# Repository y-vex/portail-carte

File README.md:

# Carte de commande pour portail à deux moteurs 24 V, avec HomeKit

Carte électronique et firmware pour piloter un portail motorisé à **deux vantaux et deux moteurs 24 V à courant
continu**, sans capteur de fin de course. Elle remplace une carte de commande du commerce tombée en panne et ajoute
Apple HomeKit, une page web de réglage et un journal des événements.

Elle a été conçue pour un portail coulissant autoportant Portaleco CT08APO-02, à deux vantaux et ouverture centrale, équipé de deux moteurs Nidec 404.854
(24 V DC), où elle remplace une carte Prastel UNIK2E.

> **Avertissement.** Un portail motorisé peut blesser gravement. Ce projet est un travail personnel, publié tel quel,
> sans aucune garantie. Il n'a fait l'objet d'aucune certification et **ne remplace pas les sécurités exigées pour un
> portail motorisé** (photocellules, limitation d'effort vérifiée à l'instrument, conformité aux normes en vigueur,
> dont l'EN 12453 en Europe). Si vous le reproduisez, vous le faites sous votre seule responsabilité.

## État du projet

- Carte **v0.4** fabriquée et assemblée, en service sur un portail coulissant Portaleco depuis novembre 2026.
- Essayé sur ce portail : mouvements complets, apprentissage des courses, détection d'obstacle par le courant
  (fermeture), photocellule (réouverture quand le faisceau est coupé à la fermeture), feu clignotant, arrêt
  progressif, HomeKit, page web, journal, mise à jour par le Wi-Fi.
- Pas encore essayé sur ce portail : entrée STOP, entrée radio,
  détection d'obstacle à l'ouverture avec un obstacle réel.
- Limite connue : par temps froid (quelques degrés), le courant des moteurs monte et s'approche des seuils appris
  par temps doux ; une fausse détection d'obstacle s'est produite une fois à l'ouverture. Les seuils sont à revoir
  selon la saison.
- Un seul portail, un seul modèle de moteur : les réglages par défaut sont des points de départ.

## La carte

| | |
| --- | --- |
| Alimentation | 24 V DC régulé (bornier J1), fusible général 15 A, protection contre l'inversion, écrêteur de surtension |
| Moteurs | 2 × pont en H TI DRV8245S réglé par SPI (borniers J2, J3), fusible 10 A par moteur, mesure du courant |
| Microcontrôleur | ESP32-S3-WROOM-1-N8, USB-C |
| Entrées (J4) | pas à pas, photocellule, radio, STOP : contacts secs, isolés par optocoupleurs, alimentés en 12 V |
| Sorties (J5) | feu clignotant et sortie auxiliaire, 12 V, commutées côté masse |
| Dimensions | 150 × 100 mm, deux couches |

- Schéma : [`schema.pdf`](schema.pdf). `schema-lisible.html` en donne une version simplifiée, par fonction
  (alimentation, commande d'un moteur, une entrée, une sortie), pour qui ne lit pas un schéma électronique.
- Projet KiCad : `kicad/`. Fichiers de fabrication : `fabrication/` et `portail-gerber.zip`.
- Nomenclature : `nomenclature.csv` ; variantes pour l'assemblage dans `fabrication/`.

**Câblage des entrées : attention au sens.** Chaque contact se branche entre `+12V_ACC` et son entrée (`PP`, `FOTO`,
`RADIO`, `STOP`). Beaucoup de cartes du commerce font l'inverse, avec des contacts qui se ferment vers un commun relié
à la masse. Un accessoire câblé pour une telle carte, par exemple un récepteur de photocellule dont le commun du
contact est ponté sur le moins de son alimentation, doit être recâblé : commun du contact sur le +12 V.
Les charges des sorties se branchent entre `+12V_OUT` et `LAMP_N` ou `AUX_N` (environ 1 A au total).

Le schéma et le circuit imprimé ne sont pas dessinés à la main : ils sont **générés par les scripts Python** de `gen/`
(`build.py` décrit le circuit, `pcb_all.py` place, route avec Freerouting et lance le contrôle des règles).

## Le firmware

Dans `firmware/portail/`, pour Arduino-ESP32 avec la bibliothèque [HomeSpan](https://github.com/HomeSpan/HomeSpan).
La notice complète est dans [`firmware/portail/LISEZMOI.md`](firmware/portail/LISEZMOI.md).

- Position estimée par le temps de fonctionnement, recalée à chaque butée.
- Butée et obstacle détectés par le courant des moteurs ; à la fermeture, un obstacle provoque la réouverture.
- Apprentissage automatique des courses et des seuils de blocage.
- Démarrage, ralentissement avant les butées et arrêt commandé progressifs.
- HomeKit : accessoire « porte de garage », plus deux capteurs d'alerte (défaut, portail resté ouvert).
- Page web sur le port 8080 : état, mesures, commandes, réglages, journal, sauvegarde et restauration des réglages.

```bash
cd firmware/portail
arduino-cli compile -b esp32:esp32:esp32s3:CDCOnBoot=cdc,FlashSize=8M,PartitionScheme=default_8MB .
arduino-cli upload  -b esp32:esp32:esp32s3:CDCOnBoot=cdc,FlashSize=8M,PartitionScheme=default_8MB -p <port> .
```

Versions utilisées : cœur `esp32:esp32` 3.3.12, HomeSpan 2.1.8.

### Sécurité réseau : à lire avant la mise en service

- La page web **n'a pas de mot de passe** : tout appareil du réseau local peut commander le portail. Ne l'exposez
  jamais sur Internet.
- La mise à jour par le Wi-Fi utilise le mot de passe par défaut de HomeSpan tant que vous ne l'avez pas changé
  (commande `O` de la console série). Changez-le, ainsi que le code d'appairage HomeKit (commande `S`).

## Régénérer la carte

Prérequis utilisés : KiCad 7 (`kicad-cli` et module Python `pcbnew`), Java 21, `xvfb-run`, Python 3 avec `cairosvg`
et `Pillow`, sous Linux. Les chemins des bibliothèques KiCad sont en dur dans `gen/kisch.py` et `gen/pcb_build.py`.
Freerouting 1.9.0 n'est pas inclus : téléchargez `freerouting.jar` depuis
[le dépôt de Freerouting](https://github.com/freerouting/freerouting) et placez-le dans `tools/`.

```bash
python3 gen/build.py        # schéma et nomenclature
python3 gen/check.py        # doit afficher OK
python3 gen/pcb_all.py      # placement, routage, contrôle des règles (plusieurs minutes)
```

## Licences

- **Matériel** (schéma, circuit imprimé, fichiers de fabrication, nomenclature, images) :
  [CERN-OHL-S v2](LICENSES/CERN-OHL-S-2.0.txt), partage à l'identique.
- **Logiciel** (firmware et scripts de `gen/`) : [GPL version 3 ou ultérieure](LICENSES/GPL-3.0-or-later.txt).

Détail et éléments tiers dans [`LICENSE.md`](LICENSE.md).

Ce projet est indépendant : il n'est ni affilié à Portaleco, Prastel, Nidec ou Apple, ni approuvé par eux. Les marques
citées appartiennent à leurs propriétaires et ne sont mentionnées que pour décrire le matériel utilisé.

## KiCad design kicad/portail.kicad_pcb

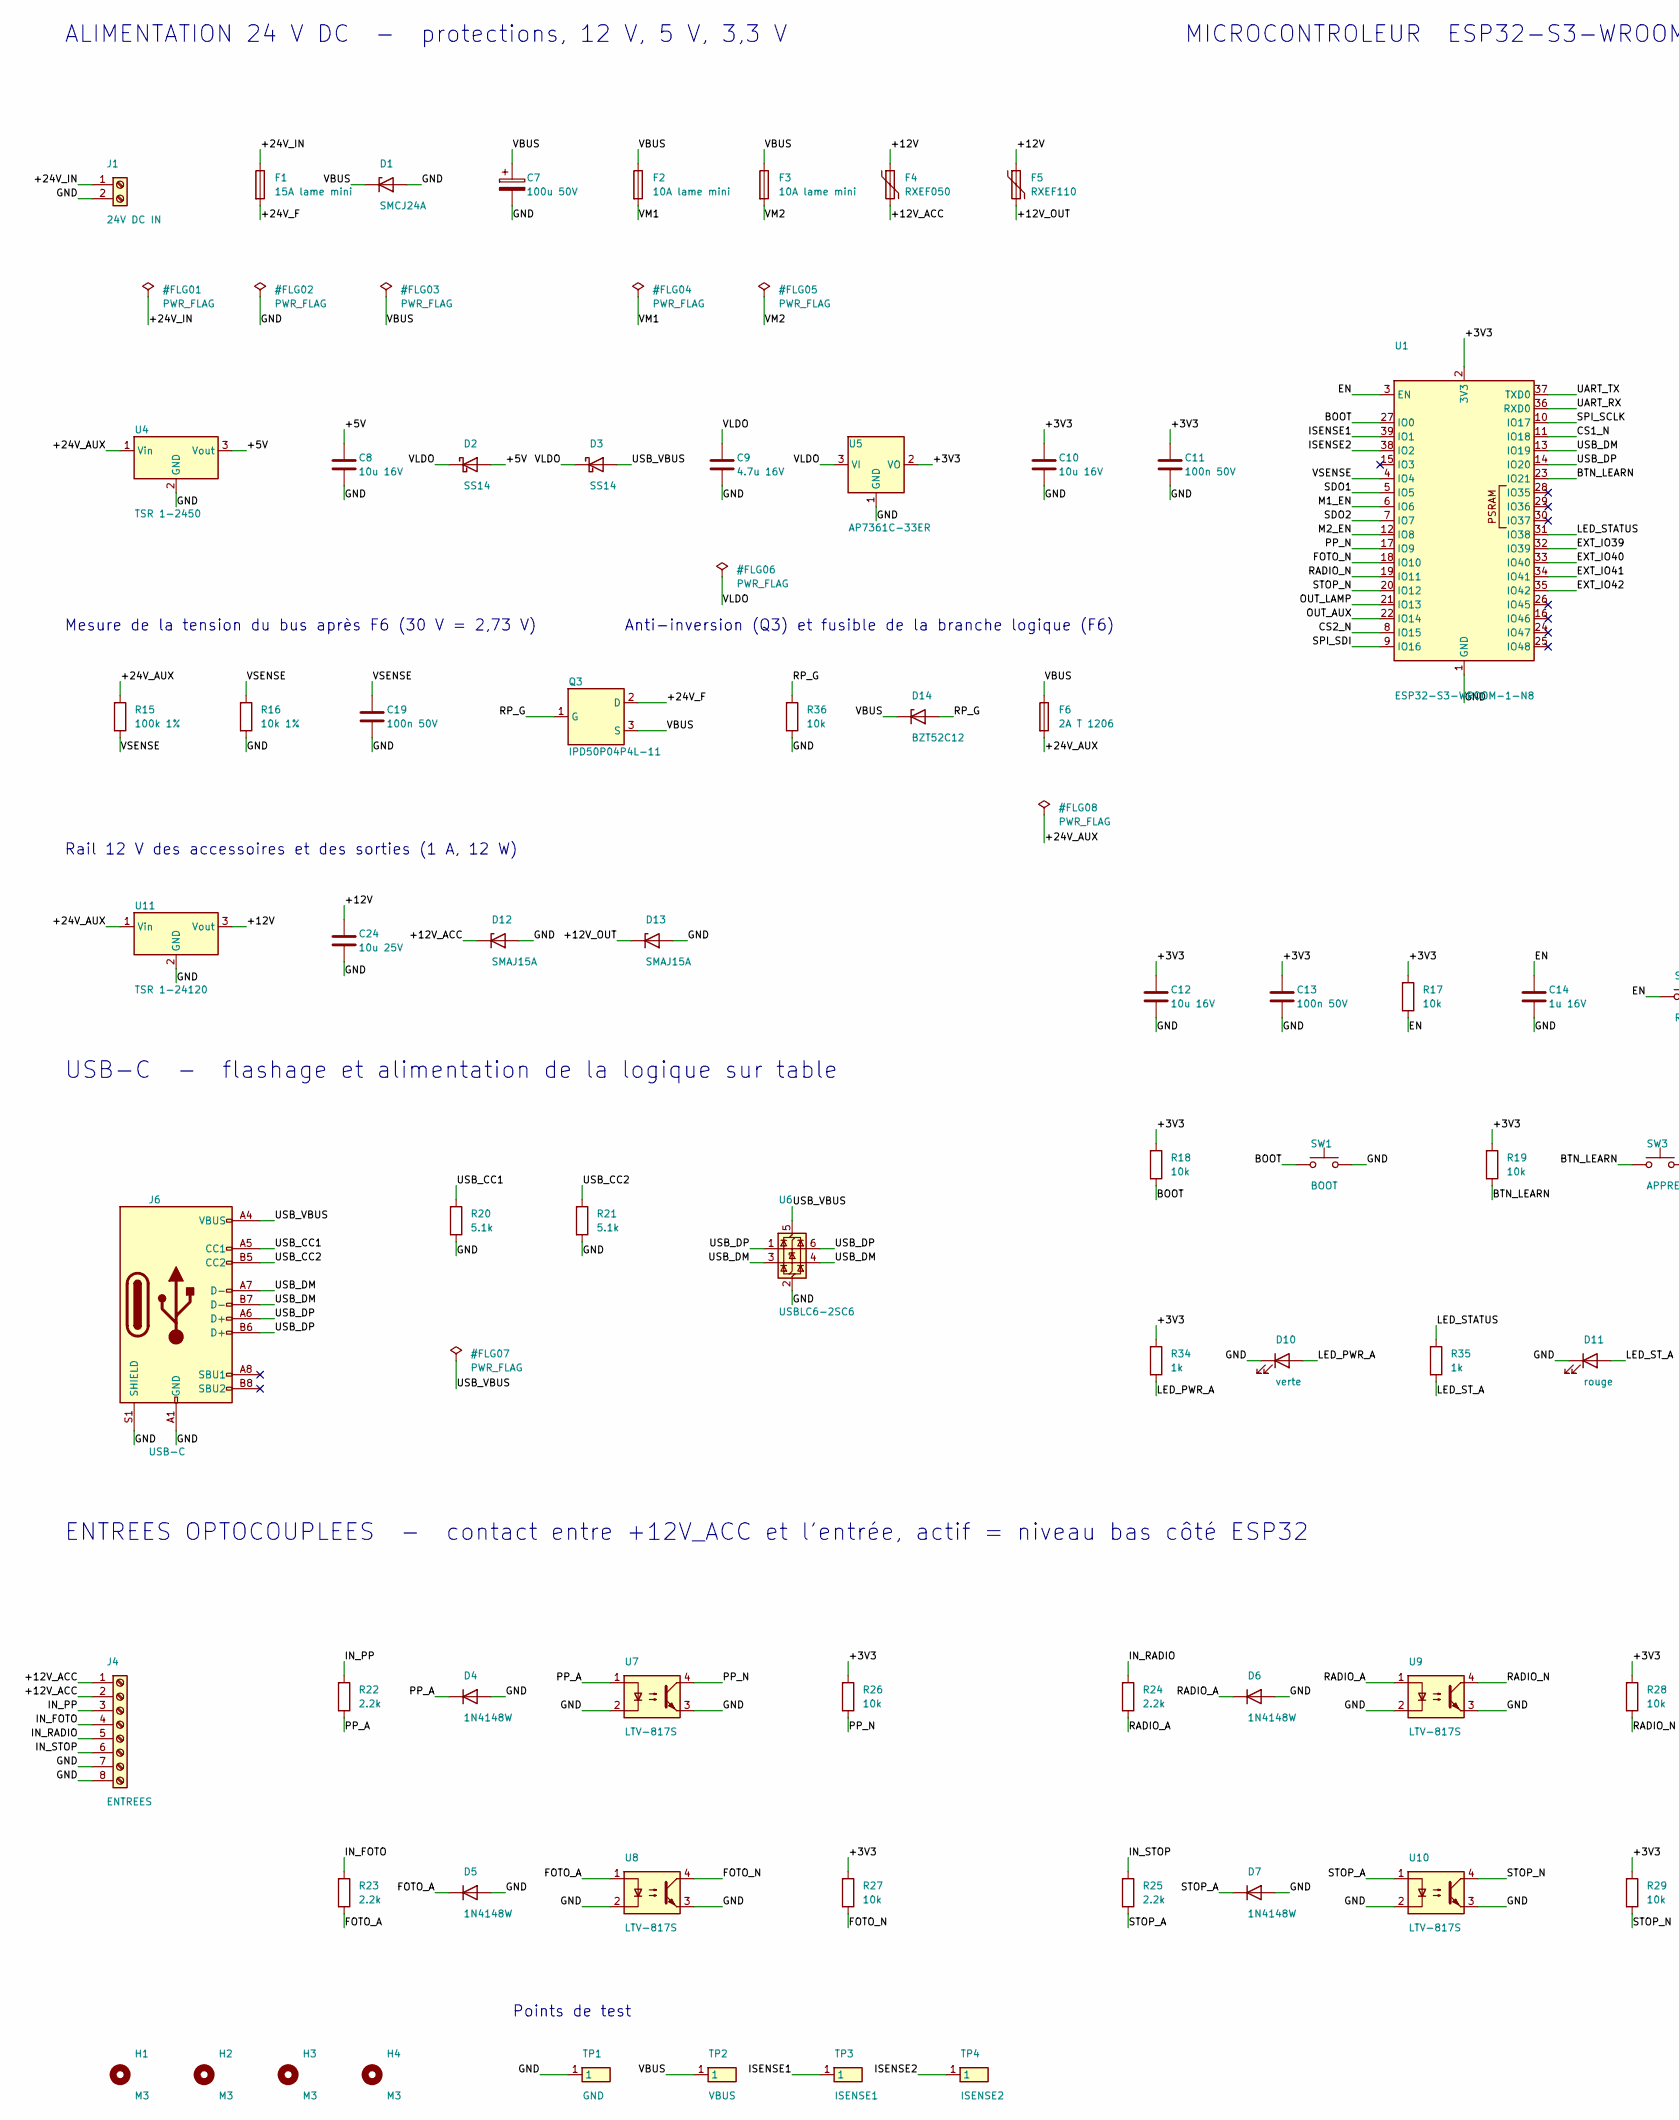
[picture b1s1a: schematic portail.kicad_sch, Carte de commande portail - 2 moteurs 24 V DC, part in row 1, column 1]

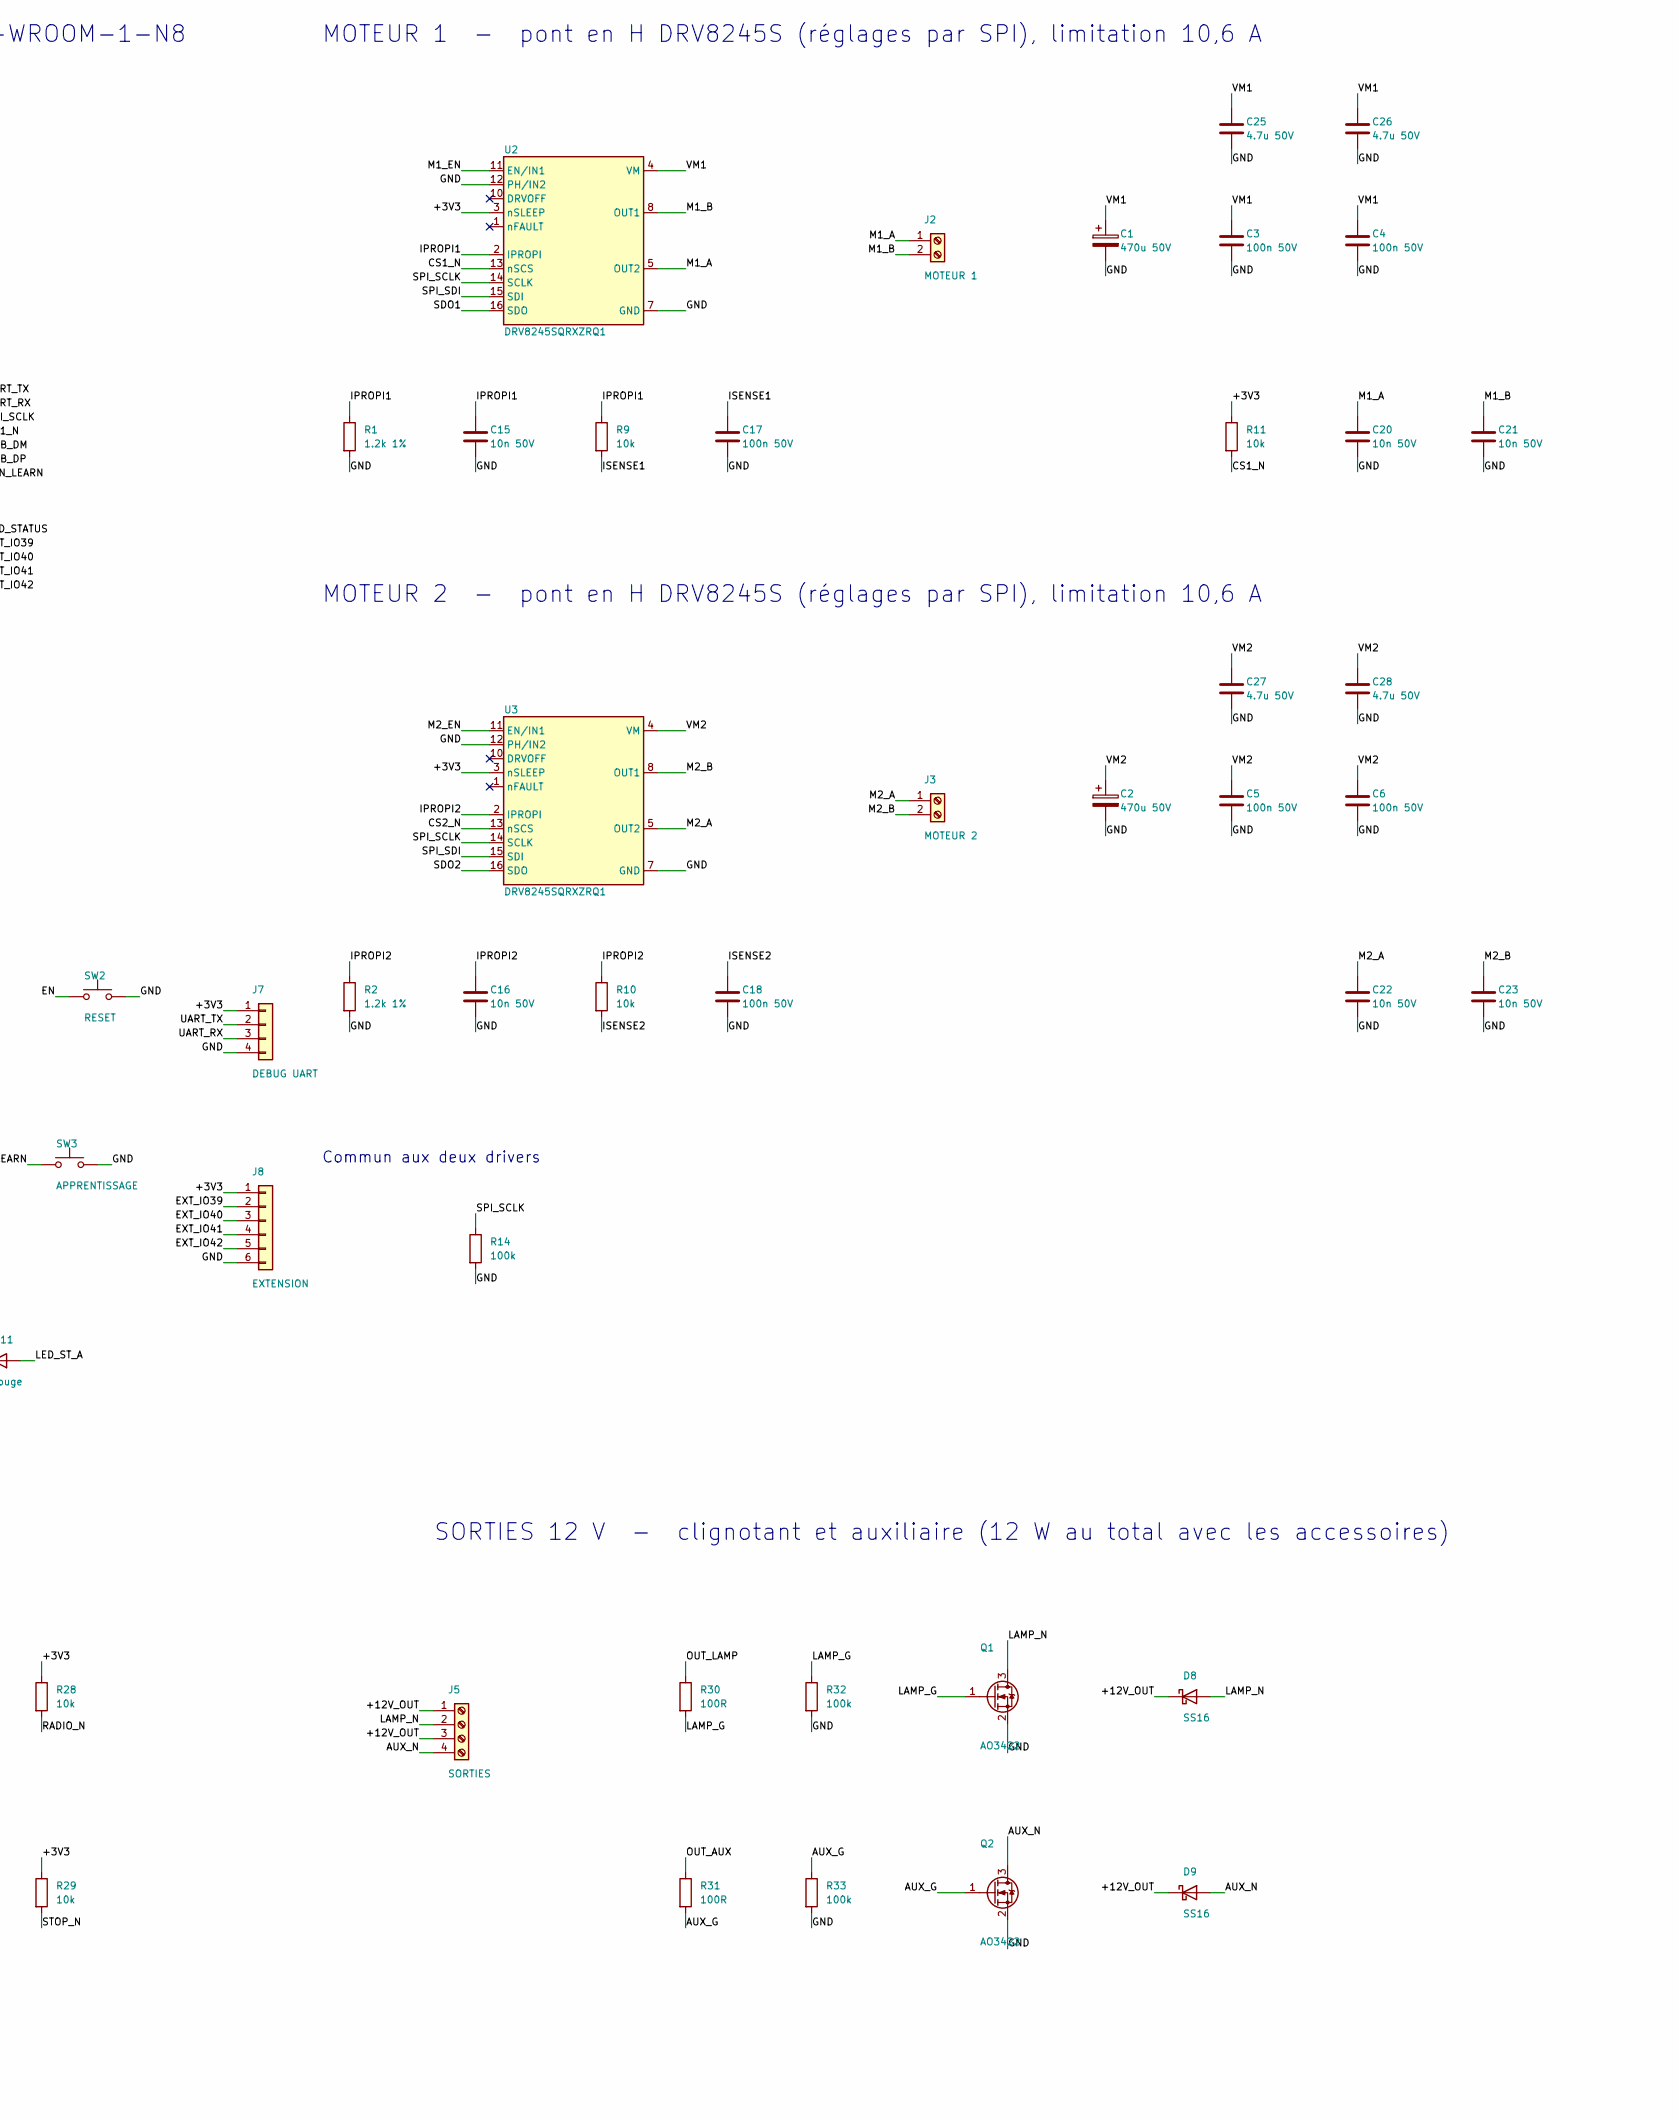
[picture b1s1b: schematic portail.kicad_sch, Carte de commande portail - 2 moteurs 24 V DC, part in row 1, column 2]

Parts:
C1, C2: 470u 50V; CP_Radial_D10.0mm_P5.00mm
C3, C4, C5, C6, C11, C13, C17, C18, C19: 100n 50V; C_0603_1608Metric
C7: 100u 50V; CP_Radial_D8.0mm_P3.50mm
C8, C10, C12: 10u 16V; C_0805_2012Metric
C9: 4.7u 16V; C_0805_2012Metric
C14: 1u 16V; C_0603_1608Metric
C15, C16, C20, C21, C22, C23: 10n 50V; C_0603_1608Metric
C24: 10u 25V; C_1206_3216Metric
C25, C26, C27, C28: 4.7u 50V; C_1206_3216Metric; MPN GRM31CR71H475KA12
D1: SMCJ24A; D_SMC; MPN SMCJ24A
D2, D3: SS14; D_SMA; MPN SS14
D4, D5, D6, D7: 1N4148W; D_SOD-123; MPN 1N4148W
D8, D9: SS16; D_SMA; MPN SS16
D10: verte; LED_0603_1608Metric
D11: rouge; LED_0603_1608Metric
D12, D13: SMAJ15A; D_SMA; MPN SMAJ15A
D14: BZT52C12; D_SOD-123; MPN BZT52C12
F1: 15A lame mini; Fuseholder_Blade_Mini_Keystone_3568
F2, F3: 10A lame mini; Fuseholder_Blade_Mini_Keystone_3568
F4: RXEF050; C_Disc_D10.5mm_W5.0mm_P5.00mm; MPN RXEF050
F5: RXEF110; C_Disc_D10.5mm_W5.0mm_P5.00mm; MPN RXEF110
F6: 2A T 1206; Fuse_1206_3216Metric; MPN 0468002.NR
H1, H2, H3, H4: M3; MountingHole_3.2mm_M3
J1: 24V DC IN; TerminalBlock_Phoenix_MKDS-1,5-2-5.08_1x02_P5.08mm_Horizont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
J2: MOTEUR 1; TerminalBlock_Phoenix_MKDS-1,5-2-5.08_1x02_P5.08mm_Horizont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
J3: MOTEUR 2; TerminalBlock_Phoenix_MKDS-1,5-2-5.08_1x02_P5.08mm_Horizont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
J4: ENTREES; TerminalBlock_Phoenix_PT-1,5-8-3.5-H_1x08_P3.50mm_Horizontal
J5: SORTIES; TerminalBlock_Phoenix_PT-1,5-4-3.5-H_1x04_P3.50mm_Horizontal
J6: USB-C; USB_C_Receptacle_GCT_USB4105-xx-A_16P_TopMnt_Horizontal; MPN USB4105-GF-A
J7: DEBUG UART; PinHeader_1x04_P2.54mm_Vertical
J8: EXTENSION; PinHeader_1x06_P2.54mm_Vertical
Q1, Q2: AO3422; SOT-23; MPN AO3422
Q3: IPD50P04P4L-11; TO-252-2; MPN IPD90P04P4L-04
R1, R2: 1.2k 1%; R_0603_1608Metric
R9, R10, R11, R17, R18, R19, R26, R27, R28, R29, R36: 10k; R_0603_1608Metric
R14, R32, R33: 100k; R_0603_1608Metric
R15: 100k 1%; R_0603_1608Metric
R16: 10k 1%; R_0603_1608Metric
R20, R21: 5.1k; R_0603_1608Metric
R22, R23, R24, R25: 2.2k; R_1206_3216Metric
R30, R31: 100R; R_0603_1608Metric
R34, R35: 1k; R_0603_1608Metric
SW1: BOOT; SW_SPST_TL3342
SW2: RESET; SW_SPST_TL3342
SW3: APPRENTISSAGE; SW_SPST_TL3342
TP1: GND; TestPoint_Pad_D1.5mm
TP2: VBUS; TestPoint_Pad_D1.5mm
TP3: ISENSE1; TestPoint_Pad_D1.5mm
TP4: ISENSE2; TestPoint_Pad_D1.5mm
U1: ESP32-S3-WROOM-1-N8; ESP32-S3-WROOM-1; MPN ESP32-S3-WROOM-1-N8
U2, U3: DRV8245SQRXZRQ1; DRV8245_VQFN-HR-16_RXZ; MPN DRV8245SQRXZRQ1
U4: TSR 1-2450; Converter_DCDC_TRACO_TSR-1_THT; MPN TSR 1-2450
U5: AP7361C-33ER; SOT-223-3_TabPin2; MPN AP7361C-33ER-13
U6: USBLC6-2SC6; SOT-23-6; MPN USBLC6-2SC6
U7, U8, U9, U10: LTV-817S; SMDIP-4_W9.53mm; MPN LTV-817S
U11: TSR 1-24120; Converter_DCDC_TRACO_TSR-1_THT; MPN TSR 1-24120

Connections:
+3V3: C10.1, C11.1, C12.1, C13.1, J7.1, J8.1, R11.1, R17.1, R18.1, R19.1, R26.1, R27.1, R28.1, R29.1, R34.1, U1.2 (3V3), U2.3 (nSLEEP), U3.3 (nSLEEP), U5.2 (VO)
+5V: C8.1, D2.2 (A), U4.3 (Vout)
+12V: C24.1, F4.1, F5.1, U11.3 (Vout)
+12V_ACC: D12.1 (K), F4.2, J4.1, J4.2
+12V_OUT: D8.1 (K), D9.1 (K), D13.1 (K), F5.2, J5.1, J5.3
+24V_AUX: F6.2, R15.1, U4.1 (Vin), U11.1 (Vin)
+24V_F: F1.2, Q3.2 (D)
+24V_IN: F1.1, J1.1
AUX_G: Q2.1 (G), R31.2, R33.1
AUX_N: D9.2 (A), J5.4, Q2.3 (D)
BOOT: R18.2, SW1.1, U1.27 (IO0)
BTN_LEARN: R19.2, SW3.1, U1.23 (IO21)
CS1_N: R11.2, U1.11 (IO18), U2.13 (nSCS)
CS2_N: U1.8 (IO15), U3.13 (nSCS)
EN: C14.1, R17.2, SW2.1, U1.3 (EN)
EXT_IO39: J8.2, U1.32 (IO39)
EXT_IO40: J8.3, U1.33 (IO40)
EXT_IO41: J8.4, U1.34 (IO41)
EXT_IO42: J8.5, U1.35 (IO42)
FOTO_A: D5.1 (K), R23.2, U8.1
FOTO_N: R27.2, U1.18 (IO10), U8.4
GND: C1.2, C2.2, C3.2, C4.2, C5.2, C6.2, C7.2, C8.2, C9.2, C10.2, C11.2, C12.2, C13.2, C14.2, C15.2, C16.2, C17.2, C18.2, C19.2, C20.2, C21.2, C22.2, C23.2, C24.2, C25.2, C26.2, C27.2, C28.2, D1.2 (A), D4.2 (A), D5.2 (A), D6.2 (A), D7.2 (A), D10.1 (K), D11.1 (K), D12.2 (A), D13.2 (A), J1.2, J4.7, J4.8, J6.A1 (GND), J6.A12 (GND), J6.B1 (GND), J6.B12 (GND), J6.S1 (SHIELD), J7.4, J8.6, Q1.2 (S), Q2.2 (S), R1.2, R2.2, R14.2, R16.2, R20.2, R21.2, R32.2, R33.2, R36.2, SW1.2, SW2.2, SW3.2, TP1.1, U1.1 (GND), U1.40 (GND), U1.41 (GND), U2.7 (GND), U2.12 (PH/IN2), U3.7 (GND), U3.12 (PH/IN2), U4.2 (GND), U5.1 (GND), U6.2 (GND), U7.2, U7.3, U8.2, U8.3, U9.2, U9.3, U10.2, U10.3, U11.2 (GND)
IN_FOTO: J4.4, R23.1
IN_PP: J4.3, R22.1
IN_RADIO: J4.5, R24.1
IN_STOP: J4.6, R25.1
IPROPI1: C15.1, R1.1, R9.1, U2.2 (IPROPI)
IPROPI2: C16.1, R2.1, R10.1, U3.2 (IPROPI)
ISENSE1: C17.1, R9.2, TP3.1, U1.39 (IO1)
ISENSE2: C18.1, R10.2, TP4.1, U1.38 (IO2)
LAMP_G: Q1.1 (G), R30.2, R32.1
LAMP_N: D8.2 (A), J5.2, Q1.3 (D)
LED_PWR_A: D10.2 (A), R34.2
LED_STATUS: R35.1, U1.31 (IO38)
LED_ST_A: D11.2 (A), R35.2
M1_A: C20.1, J2.1, U2.5 (OUT2), U2.6 (OUT2)
M1_B: C21.1, J2.2, U2.8 (OUT1), U2.9 (OUT1)
M1_EN: U1.6 (IO6), U2.11 (EN/IN1)
M2_A: C22.1, J3.1, U3.5 (OUT2), U3.6 (OUT2)
M2_B: C23.1, J3.2, U3.8 (OUT1), U3.9 (OUT1)
M2_EN: U1.12 (IO8), U3.11 (EN/IN1)
OUT_AUX: R31.1, U1.22 (IO14)
OUT_LAMP: R30.1, U1.21 (IO13)
PP_A: D4.1 (K), R22.2, U7.1
PP_N: R26.2, U1.17 (IO9), U7.4
RADIO_A: D6.1 (K), R24.2, U9.1
RADIO_N: R28.2, U1.19 (IO11), U9.4
RP_G: D14.2 (A), Q3.1 (G), R36.1
SDO1: U1.5 (IO5), U2.16 (SDO)
SDO2: U1.7 (IO7), U3.16 (SDO)
SPI_SCLK: R14.1, U1.10 (IO17), U2.14 (SCLK), U3.14 (SCLK)
SPI_SDI: U1.9 (IO16), U2.15 (SDI), U3.15 (SDI)
STOP_A: D7.1 (K), R25.2, U10.1
STOP_N: R29.2, U1.20 (IO12), U10.4
UART_RX: J7.3, U1.36 (RXD0)
UART_TX: J7.2, U1.37 (TXD0)
USB_CC1: J6.A5 (CC1), R20.1
USB_CC2: J6.B5 (CC2), R21.1
USB_DM: J6.A7 (D-), J6.B7 (D-), U1.13 (IO19), U6.3 (I/O2), U6.4 (I/O2)
USB_DP: J6.A6 (D+), J6.B6 (D+), U1.14 (IO20), U6.1 (I/O1), U6.6 (I/O1)
USB_VBUS: D3.2 (A), J6.A4 (VBUS), J6.A9 (VBUS), J6.B4 (VBUS), J6.B9 (VBUS), U6.5 (VBUS)
VBUS: C7.1, D1.1 (K), D14.1 (K), F2.1, F3.1, F6.1, Q3.3 (S), TP2.1
VLDO: C9.1, D2.1 (K), D3.1 (K), U5.3 (VI)
VM1: C1.1, C3.1, C4.1, C25.1, C26.1, F2.2, U2.4 (VM)
VM2: C2.1, C5.1, C6.1, C27.1, C28.1, F3.2, U3.4 (VM)
VSENSE: C19.1, R15.2, R16.1, U1.4 (IO4)

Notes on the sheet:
ALIMENTATION 24 V DC - protections, 12 V, 5 V, 3,3 V
Mesure de la tension du bus après F6 (30 V = 2,73 V)
Anti-inversion (Q3) et fusible de la branche logique (F6)
Rail 12 V des accessoires et des sorties (1 A, 12 W)
USB-C - flashage et alimentation de la logique sur table
MICROCONTROLEUR ESP32-S3-WROOM-1-N8
MOTEUR 1 - pont en H DRV8245S (réglages par SPI), limitation 10,6 A
MOTEUR 2 - pont en H DRV8245S (réglages par SPI), limitation 10,6 A
Commun aux deux drivers
ENTREES OPTOCOUPLEES - contact entre +12V_ACC et l'entrée, actif = niveau bas côté ESP32
SORTIES 12 V - clignotant et auxiliaire (12 W au total avec les accessoires)
Points de test

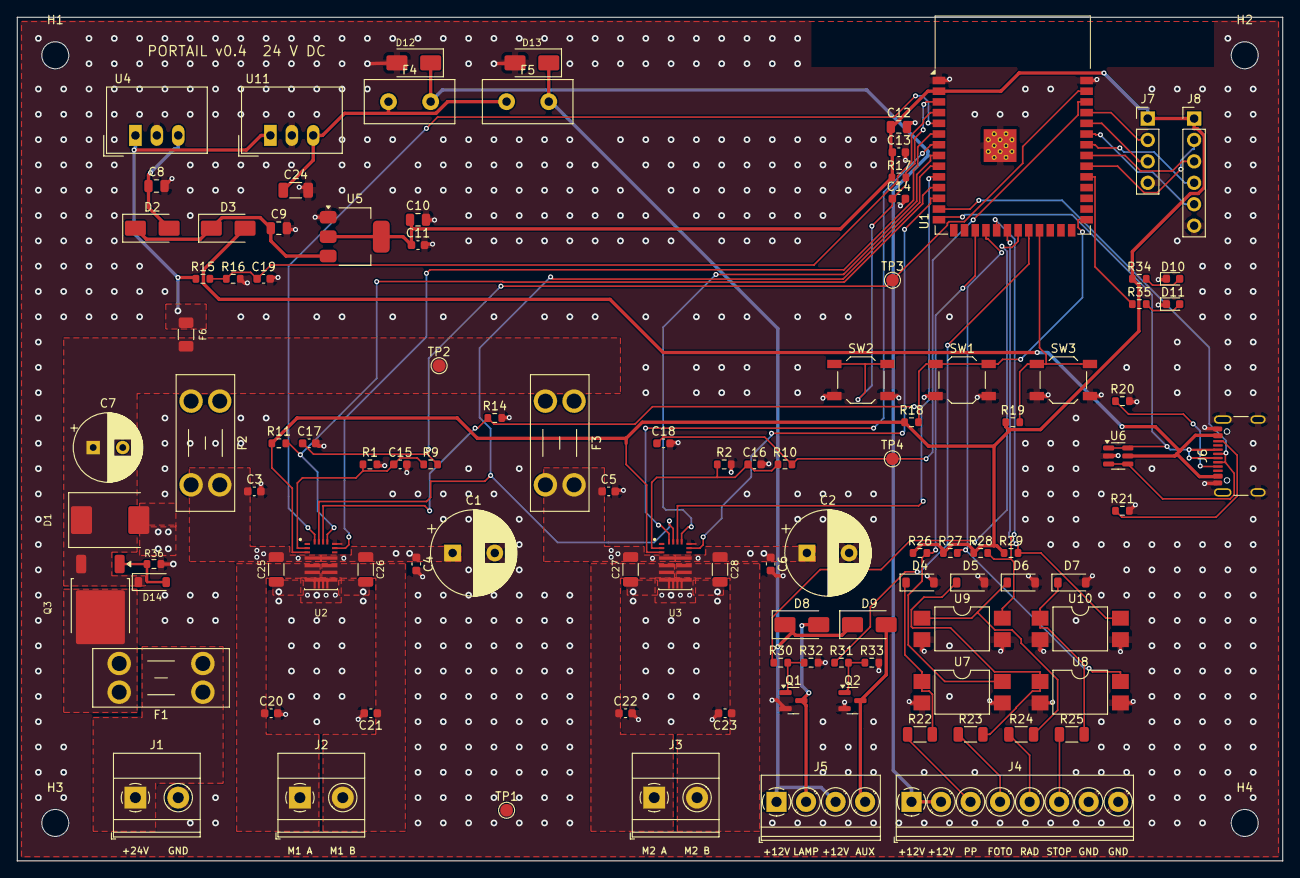
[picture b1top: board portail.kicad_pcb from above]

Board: 2 copper layers, 150.0 x 100.0 mm, 109 parts (0 on the bottom side), 66 nets.

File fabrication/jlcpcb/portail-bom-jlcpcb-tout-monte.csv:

Comment,Designator,Footprint,LCSC Part #
470u 50V UHE1H471MPD,"C1,C2",CP_Radial_D10.0mm_P5.00mm,C88733
100n 50V CL10B104KB8NNNC,"C3,C4,C5,C6,C11,C13,C17,C18,C19",C_0603_1608Metric,C1591
100u 50V UHE1H101MPD,C7,CP_Radial_D8.0mm_P3.50mm,C116229
10u 16V CL21B106KOQNNNE,"C8,C10,C12",C_0805_2012Metric,C95841
4.7u 16V CL21B475KOFNNNE,C9,C_0805_2012Metric,C107365
1u 16V CL10B105KO8NNNC,C14,C_0603_1608Metric,C59782
10n 50V CL10B103KB8NNNC,"C15,C16,C20,C21,C22,C23",C_0603_1608Metric,C1589
10u 25V CL31B106KAHNNNE,C24,C_1206_3216Metric,C14860
4.7u 50V GRM31CR71H475KA12L,"C25,C27,C26,C28",C_1206_3216Metric,C77096
SMCJ24A SMCJ24A-13-F,D1,D_SMC,C135154
SS14 SS14-E3/61T,"D2,D3",D_SMA,C2480
1N4148W 1N4148W-7-F,"D4,D5,D6,D7",D_SOD-123,C81598
SS16 SS16-E3/61T,"D8,D9",D_SMA,C183023
verte APT1608SGC,D10,LED_0603_1608Metric,C5875754
rouge APT1608EC,D11,LED_0603_1608Metric,C5554143
SMAJ15A SMAJ15A-13-F,"D12,D13",D_SMA,C110520
BZT52C12 BZT52C12-7-F,D14,D_SOD-123,C124196
15A lame mini 3568,"F1,F2,F3",Fuseholder_Blade_Mini_Keystone_3568,C3205378
RXEF050 RXEF050,F4,C_Disc_D10.5mm_W5.0mm_P5.00mm,C76399
RXEF110 RXEF110,F5,C_Disc_D10.5mm_W5.0mm_P5.00mm,C3760872
2A T 1206 0468002.NR,F6,Fuse_1206_3216Metric,C187611
24V DC IN 1715721,"J1,J2,J3","TerminalBlock_Phoenix_MKDS-1,5-2-5.08_1x02_P5.08mm_Horizontal",C480516
ENTREES 1984675,"J4A,J4B,J5","TerminalBlock_Phoenix_PT-1,5-8-3.5-H_1x08_P3.50mm_Horizontal",C5144867
USB-C USB4105-GF-A,J6,USB_C_Receptacle_GCT_USB4105-xx-A_16P_TopMnt_Horizontal,C3020560
DEBUG UART 61300411121,J7,PinHeader_1x04_P2.54mm_Vertical,C5184785
EXTENSION 61300611121,J8,PinHeader_1x06_P2.54mm_Vertical,C5444523
AO3422 AO3422,"Q1,Q2",SOT-23,C37130
IPD50P04P4L-11 IPD50P04P4L11ATMA2,Q3,TO-252-2,C386372
1.2k 1% RC0603FR-071K2L,"R1,R2",R_0603_1608Metric,C22765
10k RC0603FR-0710KL,"R9,R10,R17,R18,R19,R26,R27,R28,R29,R11,R16,R36",R_0603_1608Metric,C25804
100k RC0603FR-07100KL,"R14,R15,R32,R33",R_0603_1608Metric,C25803
5.1k RC0603FR-075K1L,"R20,R21",R_0603_1608Metric,C23186
2.2k RC1206FR-072K2L,"R22,R23,R24,R25",R_1206_3216Metric,C114933
100R RC0603FR-07100RL,"R30,R31",R_0603_1608Metric,C22775
1k RC0603FR-071KL,"R34,R35",R_0603_1608Metric,C21190
BOOT TL3342F450QG,"SW1,SW2,SW3",SW_SPST_TL3342,C2886897
ESP32-S3-WROOM-1-N8 ESP32-S3-WROOM-1-N8,U1,ESP32-S3-WROOM-1,C2913198
DRV8245SQRXZRQ1 DRV8245SQRXZRQ1,"U2,U3",DRV8245_VQFN-HR-16_RXZ,C6602055
TSR 1-2450 TSR 1-2450,U4,Converter_DCDC_TRACO_TSR-1_THT,C6886877
AP7361C-33ER AP7361C-33ER-13,U5,SOT-223-3_TabPin2,C3743528
USBLC6-2SC6 USBLC6-2SC6,U6,SOT-23-6,C7519
LTV-817S LTV-817S-TA1,"U7,U8,U9,U10",SMDIP-4_W9.53mm,C109227
TSR 1-24120 TSR 1-24120,U11,Converter_DCDC_TRACO_TSR-1_THT,C5369648
